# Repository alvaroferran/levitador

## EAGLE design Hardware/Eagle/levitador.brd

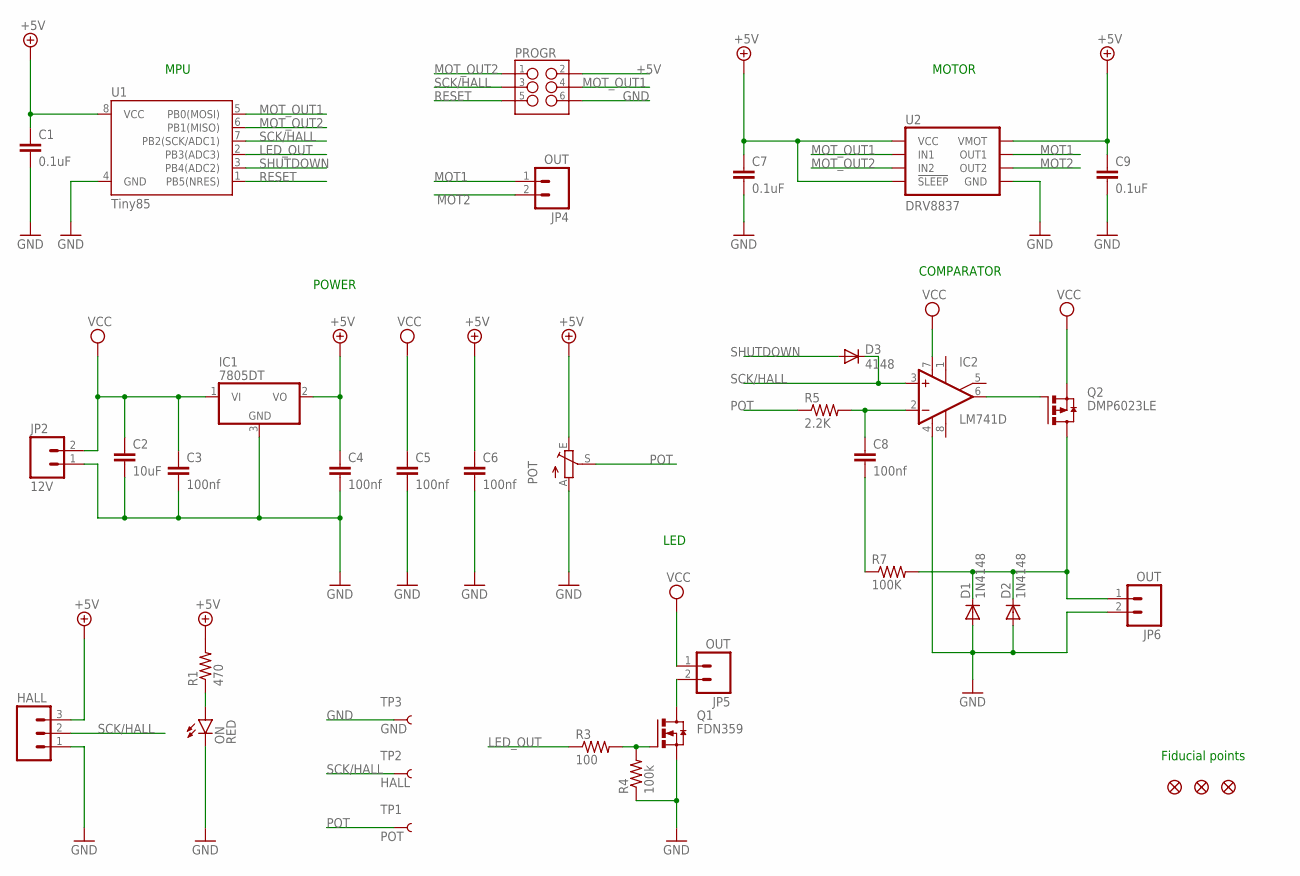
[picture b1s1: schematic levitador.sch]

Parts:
C1, C7, C9: 0.1uF; 0402-CAP
C2: 10uF; 1206
C3, C4, C5, C6, C8: 100nf; C0805
D1, D2: 1N4148; MINIMELF
D3: 4148; MICROMELF-W
FID1, FID2, FID3: FIDUCIAL1X2; FIDUCIAL-1X2
HALL: M03LOCK; 1X03_LOCK
IC1: 7805DT; TO252
IC2: LM741D; SO08
JP2: 12V; MOLEX-1X2
JP4, JP5, JP6: OUT; MOLEX-1X2
ON: RED; LED-0603
POT: TRIM_EU-B64W; B64W
PROGR: M03X2; 2X3_SMD
Q1: FDN359; SUPER-SOT3
Q2: DMP6023LE; SOT223
R1: 470; 0805
R3: 100; 0805
R4: 100k; 0805
R5: 2.2K; 0805
R7: 100K; 0805
TP1: POT; TP_15TH
TP2: HALL; TP_15TH
TP3: GND; TP_15TH
U1: Tiny85; SO08-EIAJ
U2: DRV8837; DSG

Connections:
+5V: C1.1, C4.1, C6.1, C7.1, C9.1, HALL.3, IC1.2 (VO), POT.E, PROGR.2, R1.2, U1.8 (VCC), U2.1 (VMOT), U2.7 (!SLEEP), U2.8 (VCC)
GND: C1.2, C2.2, C3.2, C4.2, C5.2, C6.2, C7.2, C9.2, D1.A, D2.A, HALL.1, IC1.3 (GND), IC2.4 (V-), JP2.1, JP6.2, ON.C, POT.A, PROGR.6, Q1.2 (S), R4.1, TP3.P$1, U1.4 (GND), U2.4 (GND), U2.PAD (GND)
LED_OUT: R3.1, U1.2 (PB3(ADC3))
MOT1: JP4.1, U2.2 (OUT1)
MOT2: JP4.2, U2.3 (OUT2)
MOT_OUT1: PROGR.4, U1.5 (PB0(MOSI)), U2.6 (IN1)
MOT_OUT2: PROGR.1, U1.6 (PB1(MISO)), U2.5 (IN2)
unnamed: C8.2, R7.1
unnamed: ON.A, R1.1
unnamed: C8.1, IC2.2 (-IN), R5.2
unnamed: Q1.1 (G), R3.2, R4.2
unnamed: JP5.2, Q1.3 (D)
unnamed: D1.C, D2.C, JP6.1, Q2.2 (D), Q2.4 (D), R7.2
unnamed: IC2.6 (OUT), Q2.1 (G)
POT: POT.S, R5.1, TP1.P$1
RESET: PROGR.5, U1.1 (PB5(NRES))
SCK/HALL: D3.C, HALL.2, IC2.3 (+IN), PROGR.3, TP2.P$1, U1.7 (PB2(SCK/ADC1))
SHUTDOWN: D3.A, U1.3 (PB4(ADC2))
VCC: C2.1, C3.1, C5.1, IC1.1 (VI), IC2.7 (V+), JP2.2, JP5.1, Q2.3 (S)

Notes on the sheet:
Fiducial points
MPU
POWER
COMPARATOR
MOTOR
LED

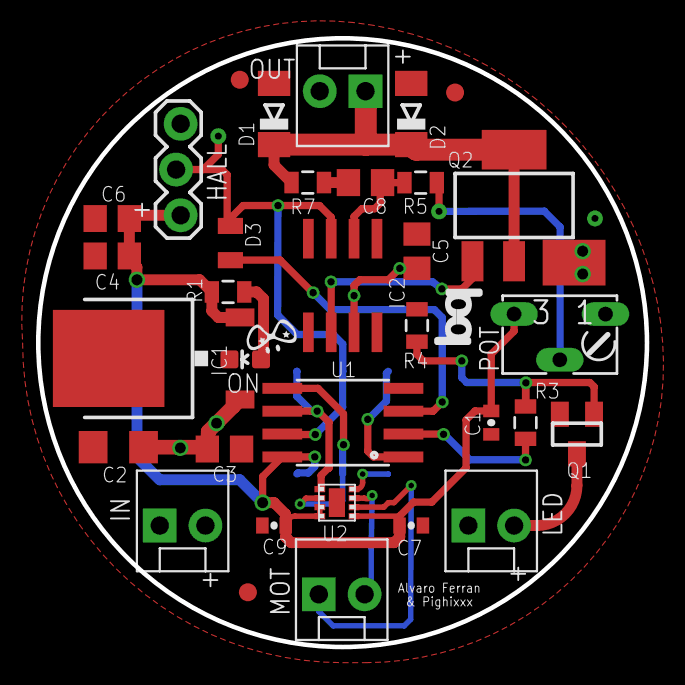
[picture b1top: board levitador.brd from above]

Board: 2 copper layers, 33.8 x 33.8 mm, 37 parts (1 on the bottom side), 19 nets.

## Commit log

2016-10-22 Files added

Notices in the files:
parts and their libraries:
SparkFun-Capacitors: Licensing: Creative Commons ShareAlike 4.0 International - https://creativecommons.org/licenses/by-sa/4.0
SparkFun-Resistors: Licensing: CC v3.0 Share-Alike You are welcome to use this library for commercial purposes.
